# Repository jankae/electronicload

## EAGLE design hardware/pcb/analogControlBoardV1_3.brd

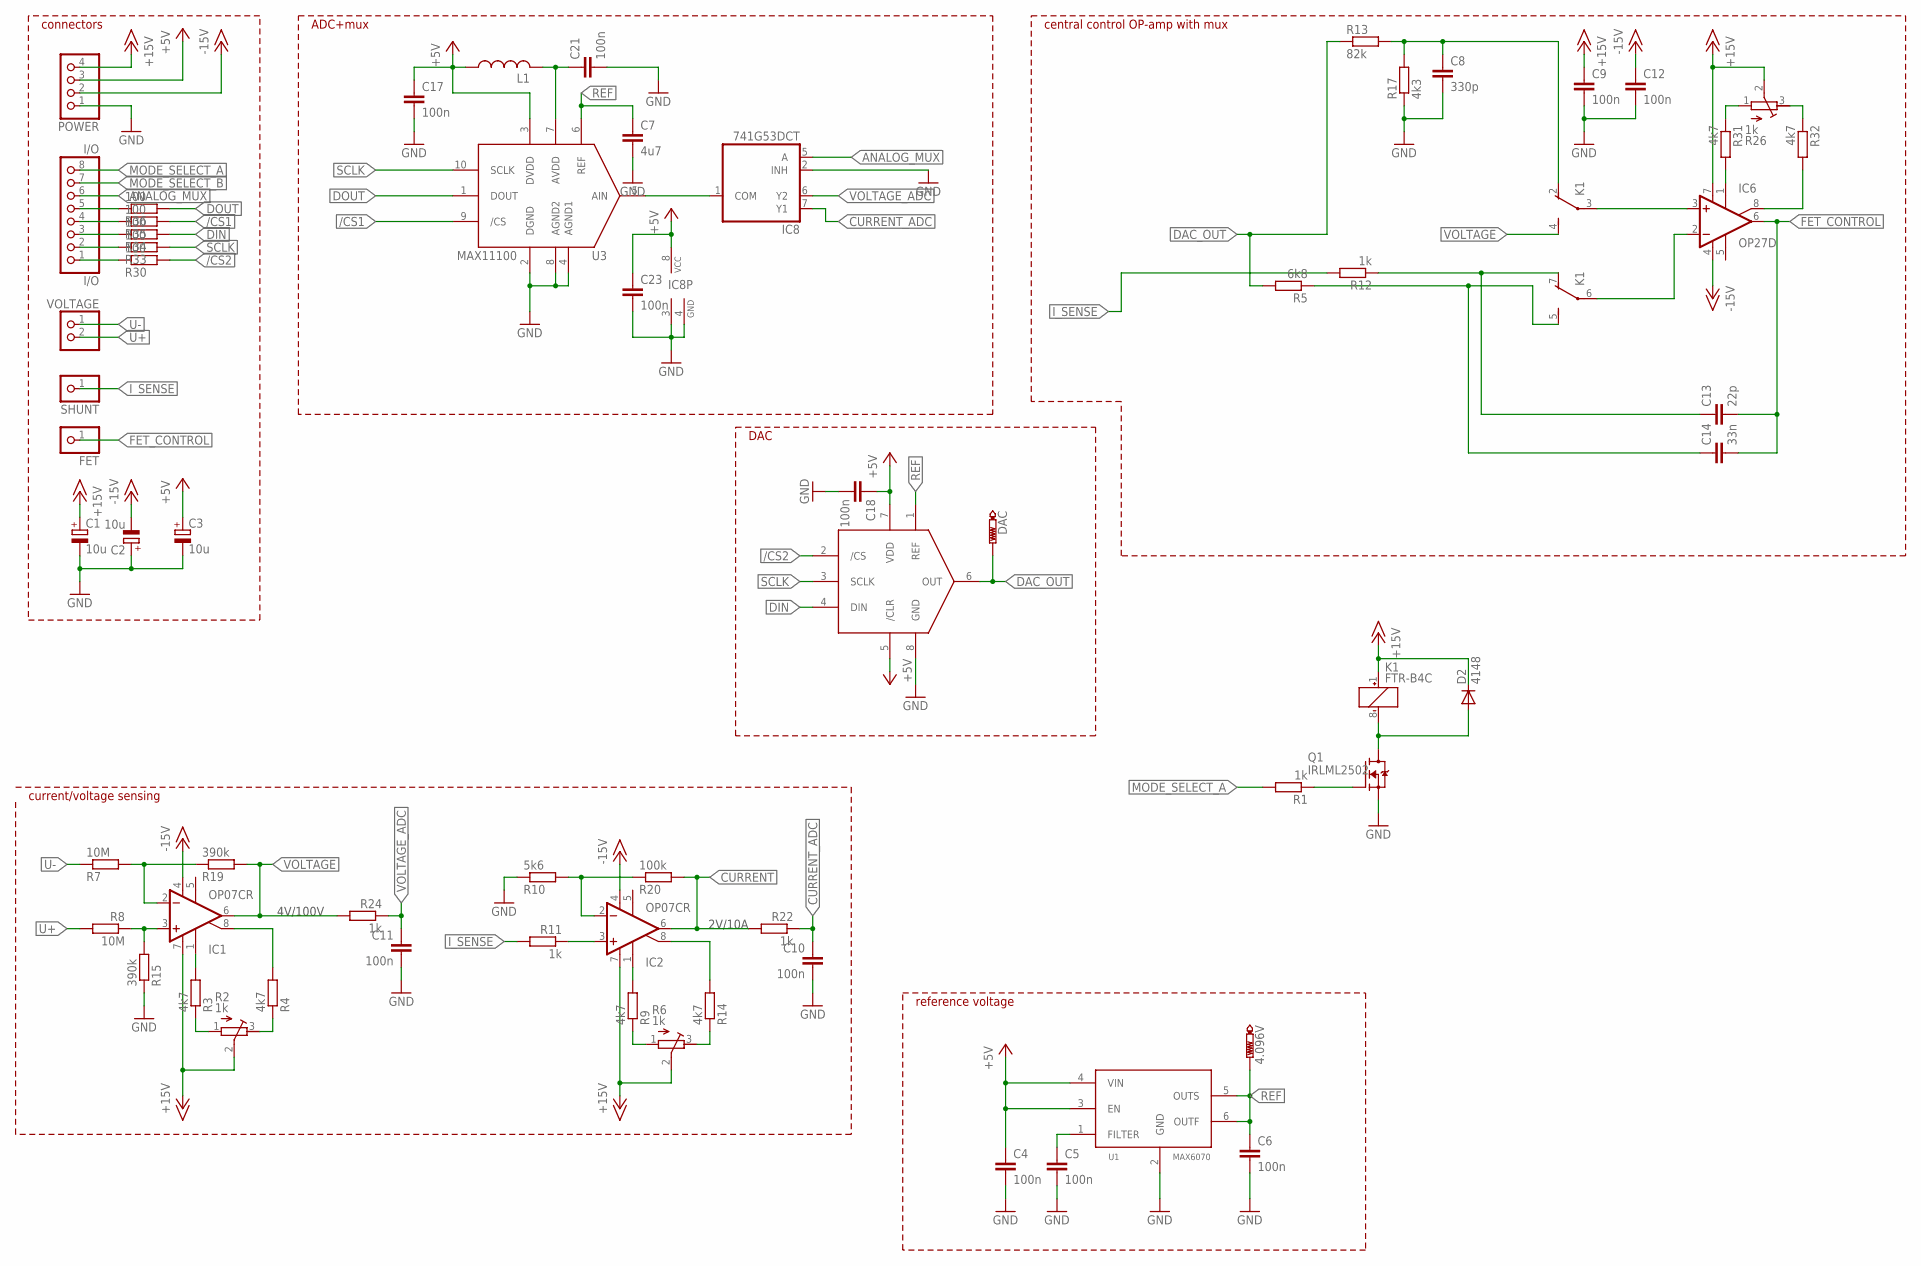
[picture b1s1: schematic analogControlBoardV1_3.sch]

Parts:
4.096V: PTR1TP14R; TP14R
C1, C2, C3: 10u; 153CLV-0505
C4, C5, C6, C9, C10, C11, C12, C17, C18, C21, C23: 100n; C0603K
C7: 4u7; C0805
C8: 330p; C0603K
C13: 22p; C0603K
C14: 33n; C0603K
D2: 4148; SOD123
DAC: PTR1TP14R; TP14R
FET: PINHD-1X1; 1X01
I/O: I/O; 1X08
IC1, IC2: OP07CR; SO08
IC6: OP27D; SO08
IC8: 741G53DCT; DCT_R-PDSO-G8
K1: FTR-B4C
L1: INDUCTOR0603; R0603
POWER: PINHD-1X4; 1X04
Q1: IRLML2502; SOT23-3
R1, R11, R12, R22, R24: 1k; R0603
R2, R6, R26: 1k; RTRIM64W
R3, R4, R9, R14, R31, R32: 4k7; R0603
R5: 6k8; R0603
R7, R8: 10M; R0603
R10: 5k6; R0603
R13: 82k; R0603
R15, R19: 390k; R0603
R17: 4k3; R0603
R20: 100k; R0603
R30, R33, R34, R35, R36: 100; R0603
SHUNT: PINHD-1X1; 1X01
U1: MAX6070; SOT23-6L
U2: MAX5216; UMAX8
U3: MAX11100; UMAX10
VOLTAGE: PINHD-1X2; 1X02

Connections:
+5V: C3.+, C4.1, C17.1, C18.1, C23.1, IC8.8 (VCC), L1.1, POWER.3, U1.3 (EN), U1.4 (VIN), U2.5 (/CLR), U2.7 (VDD), U3.3 (DVDD)
+15V: C1.+, C9.1, D2.C, IC1.7 (V+), IC2.7 (V+), IC6.7 (V+), K1.1 (+), POWER.4, R2.2 (S), R6.2 (S), R26.2 (S)
-15V: C2.-, C12.1, IC1.4 (V-), IC2.4 (V-), IC6.4 (V-), POWER.2
/CS1: R35.2, U3.9 (/CS)
/CS2: R30.2, U2.2 (/CS)
ANALOG_MUX: I/O.6, IC8.5 (A)
CURRENT: IC2.6 (OUT), R20.2, R22.2
CURRENT_ADC: C10.1, IC8.7 (Y1), R22.1
DAC_OUT: DAC.TP, R5.2, R13.1, U2.6 (OUT)
DIN: R34.2, U2.4 (DIN)
DOUT: R36.2, U3.1 (DOUT)
FET_CONTROL: C13.2, C14.2, FET.1, IC6.6 (OUT)
GND: C1.-, C2.+, C3.-, C4.2, C5.2, C6.2, C7.2, C8.2, C9.2, C10.2, C11.2, C12.2, C17.2, C18.2, C21.2, C23.2, IC8.2 (INH), IC8.3 (GND), IC8.4 (GND), POWER.1, Q1.2 (S), R10.1, R15.1, R17.1, U1.2 (GND), U2.8 (GND), U3.2 (DGND), U3.4 (AGND1), U3.8 (AGND2)
I_SENSE: R11.2, R12.2, SHUNT.1
MODE_SELECT_A: I/O.8, R1.2
MODE_SELECT_B: I/O.7
unnamed: C8.1, K1.2 (O), R13.2, R17.2
unnamed: D2.A, K1.8 (-), Q1.3 (D)
unnamed: Q1.1 (G), R1.1
unnamed: C13.1, K1.7 (O), R12.1
unnamed: IC2.3 (+IN), R11.1
unnamed: IC2.2 (-IN), R10.2, R20.1
unnamed: R2.1 (E), R3.1
unnamed: IC1.8 (ON2), R4.2
unnamed: R26.3 (A), R32.1
unnamed: R2.3 (A), R4.1
unnamed: IC6.1 (ON1), R31.2
unnamed: IC1.1 (ON1), R3.2
unnamed: R6.1 (E), R9.1
unnamed: IC2.8 (ON2), R14.2
unnamed: R6.3 (A), R14.1
unnamed: IC2.1 (ON1), R9.2
unnamed: I/O.5, R36.1
unnamed: I/O.4, R35.1
unnamed: I/O.3, R34.1
unnamed: I/O.2, R33.1
unnamed: I/O.1, R30.1
unnamed: IC6.3 (+IN), K1.3
unnamed: C5.1, U1.1 (FILTER)
unnamed: IC6.2 (-IN), K1.6
unnamed: C14.1, K1.5 (S), R5.1
unnamed: R26.1 (E), R31.1
unnamed: IC6.8 (ON2), R32.2
unnamed: C21.1, L1.2, U3.7 (AVDD)
unnamed: IC8.1 (COM), U3.5 (AIN)
unnamed: IC1.3 (+IN), R8.1, R15.2
unnamed: IC1.2 (-IN), R7.2, R19.1
REF: 4.096V.TP, C6.1, C7.1, U1.5 (OUTS), U1.6 (OUTF), U2.1 (REF), U3.6 (REF)
SCLK: R33.2, U2.3 (SCLK), U3.10 (SCLK)
U+: R8.2, VOLTAGE.2
U-: R7.1, VOLTAGE.1
VOLTAGE: IC1.6 (OUT), K1.4 (S), R19.2, R24.2
VOLTAGE_ADC: C11.1, IC8.6 (Y2), R24.1

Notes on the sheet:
2V/10A
4V/100V
connectors
ADC+mux
DAC
current/voltage sensing
reference voltage
central control OP-amp with mux

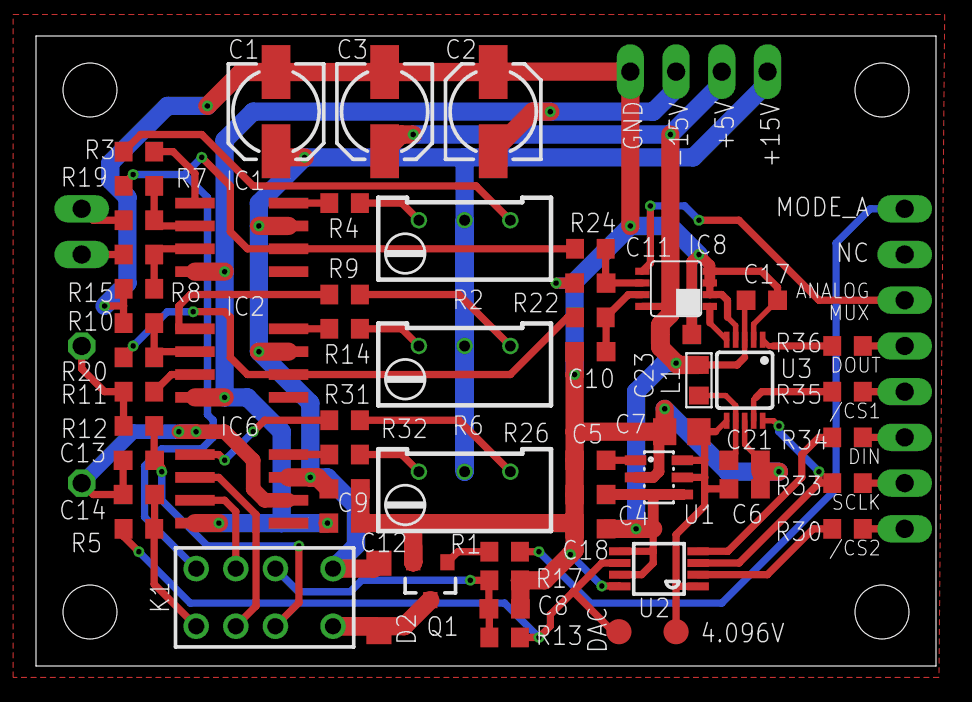
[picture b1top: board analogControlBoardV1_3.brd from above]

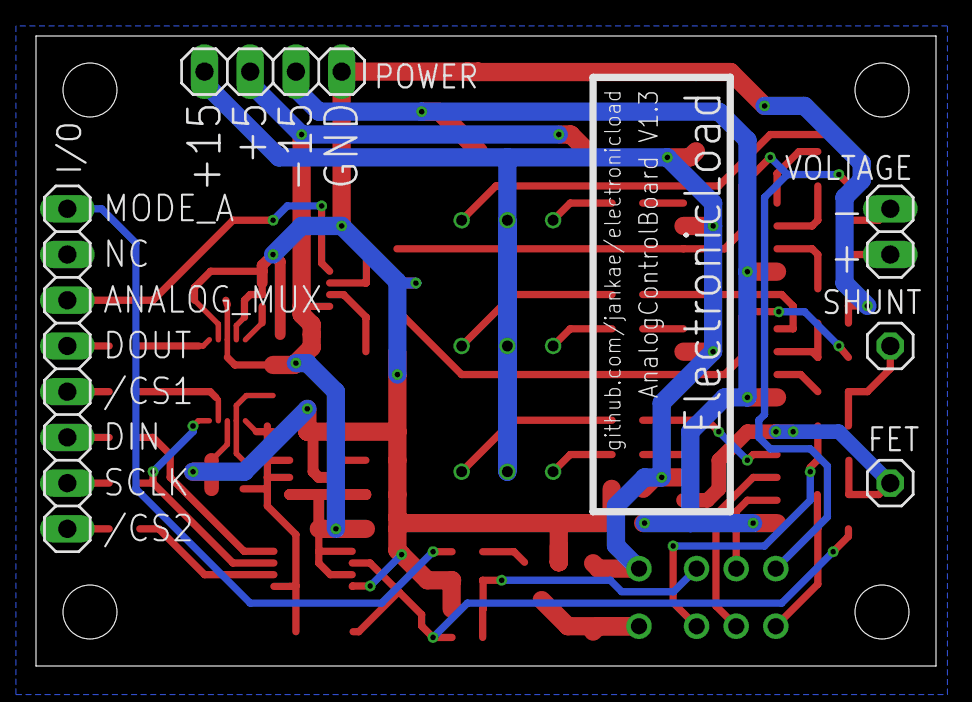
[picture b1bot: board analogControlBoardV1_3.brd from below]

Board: 2 copper layers, 50.0 x 35.0 mm, 64 parts (5 on the bottom side), 52 nets.

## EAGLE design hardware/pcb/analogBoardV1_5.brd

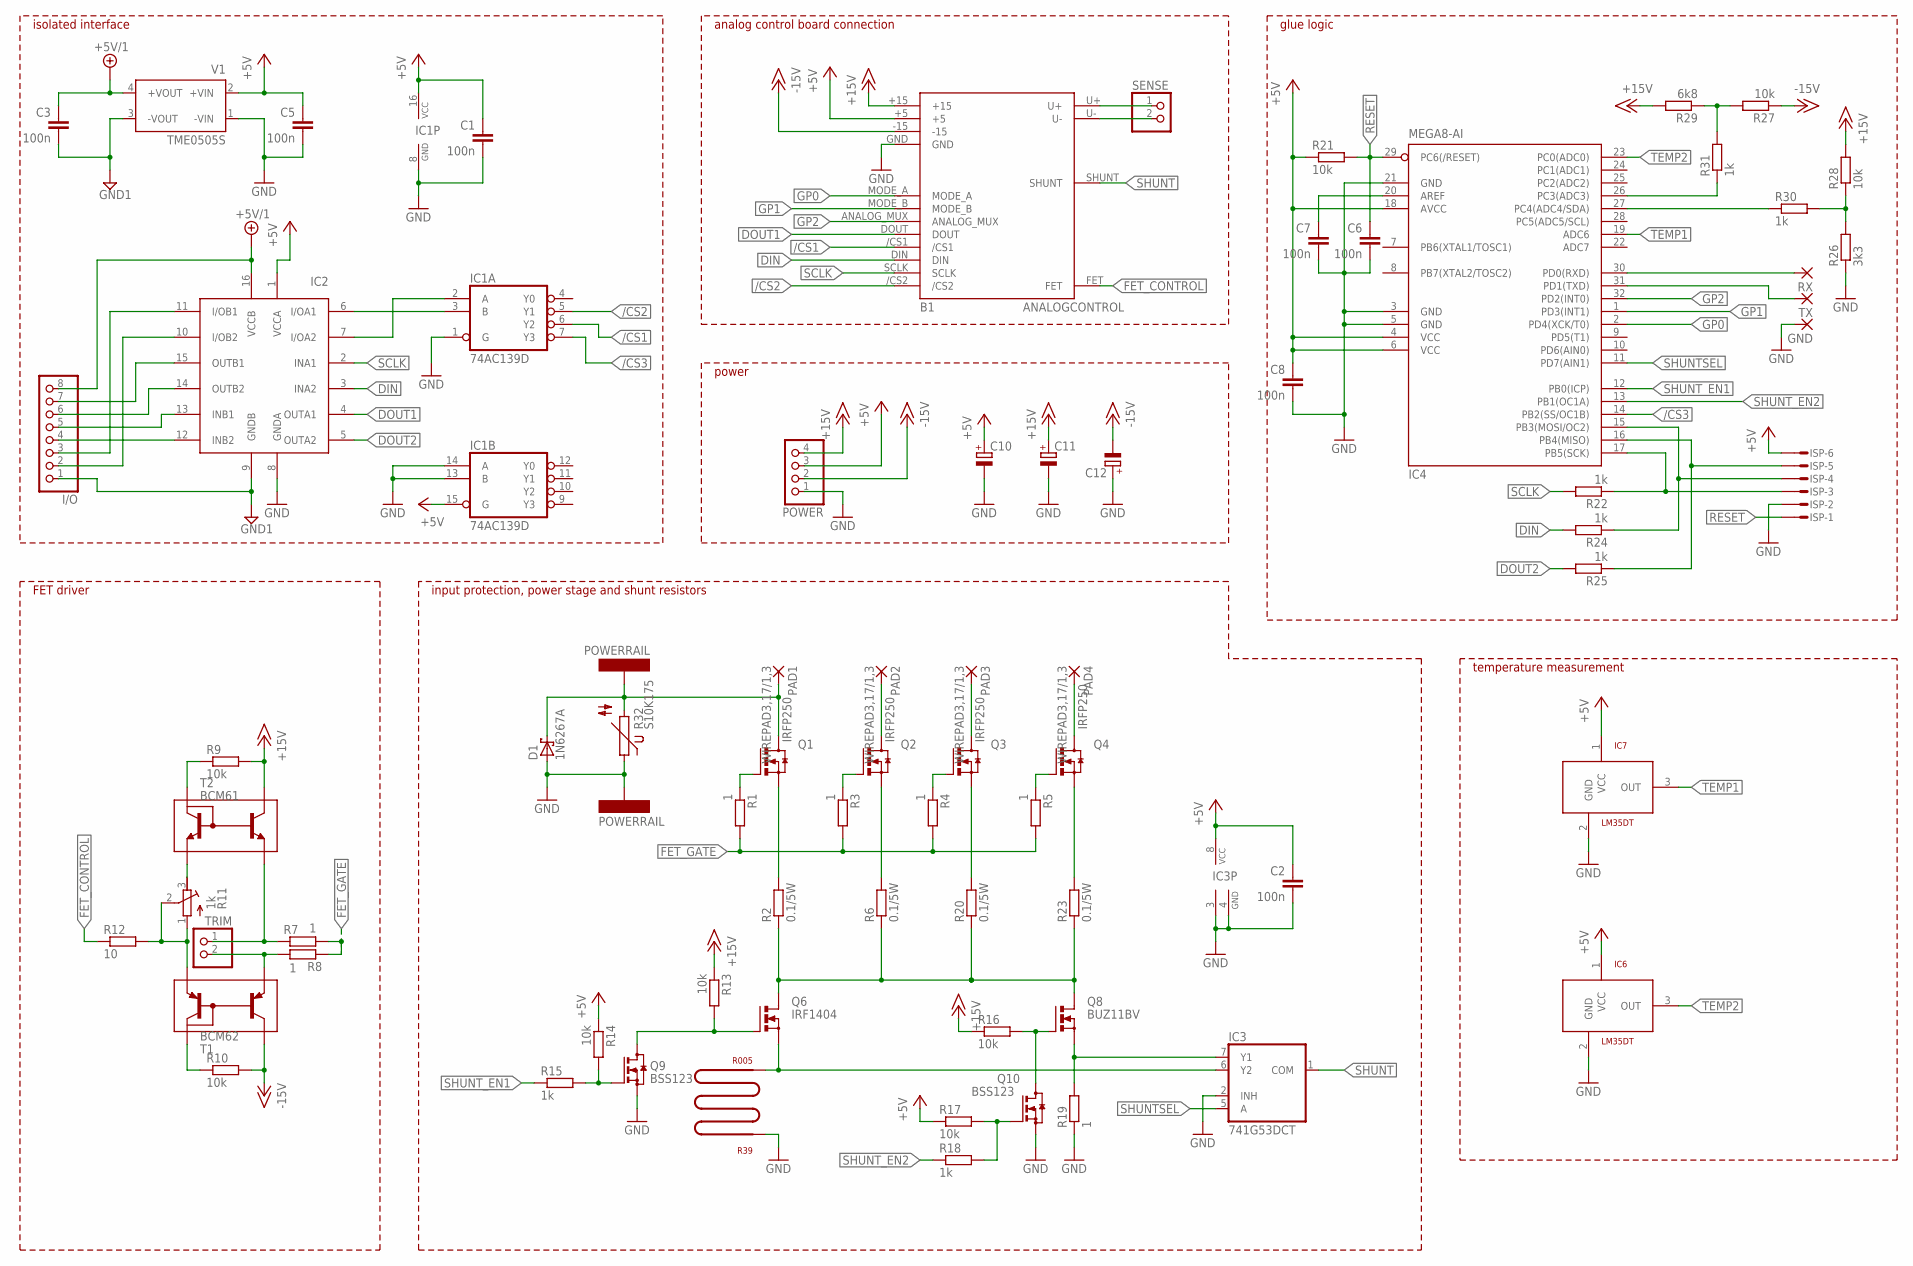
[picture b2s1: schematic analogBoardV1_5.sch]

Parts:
B1: ANALOGCONTROL
C1, C2, C3, C5, C6, C7, C8: 100n; C0603K
C10, C11, C12: CPOL-EUE2.5-6; E2,5-6
D1: 1N6267A; C4111-15
GND: SMD2; SMD1,27-2,54
I/O: PINHD-1X8; 1X08
IC1: 74AC139D; SO16
IC2: MAX14850; SOIC16N
IC3: 741G53DCT; DCT_R-PDSO-G8
IC4: MEGA8-AI; TQFP32-08
IC6, IC7: LM35DT; TO220V
ISP: MICROMATCH-6SMF; MMT-F-SMD-6
PAD1, PAD2, PAD3, PAD4: WIREPAD3,17/1,3; 3,17/1,3
POWER: PINHD-1X4; 1X04
Q1, Q2, Q3, Q4: IRFP250; TO-247AD-V
Q6: IRF1404; TO220BV
Q8: BUZ11BV; TO220BV
Q9, Q10: BSS123; SOT23
R1, R3, R4, R5, R7, R8: 1; R0603
R2, R6, R20, R23: 0.1/5W; 5WAXIAL_H
R9, R10, R13, R14, R16, R17, R21, R27, R28: 10k; R0603
R11: 1k; RTRIM64W
R12: 10; R0603
R15, R18, R22, R24, R25, R30, R31: 1k; R0603
R19: 1; 0414/15
R26: 3k3; R0603
R29: 6k8; R0603
R32: S10K175
R39: R005; PWR4412-2S
RX: SMD2; SMD1,27-2,54
SENSE: PINHD-1X2; 1X02
T1: BCM62; SOT143B
T2: BCM61; SOT143B
TRIM: PINHD-1X2; 1X02
TX: SMD2; SMD1,27-2,54
U$1, U$2: POWERRAIL
V1: TME0505S; TME

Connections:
+5V: B1.+5, C1.1, C2.1, C5.1, C8.1, C10.+, IC1.15 (G), IC1.16 (VCC), IC2.1 (VCCA), IC3.8 (VCC), IC4.4 (VCC), IC4.6 (VCC), IC4.18 (AVCC), IC6.1 (VCC), IC7.1 (VCC), ISP.6, POWER.3, R14.1, R17.1, R21.1, V1.2 (+VIN)
+5V/1: C3.1, I/O.8, IC2.16 (VCCB), V1.4 (+VOUT)
+15V: B1.+15, C11.+, POWER.4, R9.2, R13.1, R16.1, R28.2, R29.2, T2.2
-15V: B1.-15, C12.-, POWER.2, R10.2, R27.1, T1.2
/CS1: B1./CS1, IC1.6 (Y2)
/CS2: B1./CS2, IC1.5 (Y1)
/CS3: IC1.7 (Y3), IC4.14 (PB2(SS/OC1B))
DIN: B1.DIN, IC2.3 (INA2), R24.2
DOUT1: B1.DOUT, IC2.4 (OUTA1)
DOUT2: IC2.5 (OUTA2), R25.2
FET_CONTROL: B1.FET, R12.1
FET_GATE: R1.2, R3.2, R4.2, R5.2, R7.2, R8.1
GND: B1.GND, C1.2, C2.2, C5.2, C6.2, C7.2, C8.2, C10.-, C11.-, C12.+, D1.A, GND.1, IC1.1 (G), IC1.8 (GND), IC1.13 (B), IC1.14 (A), IC2.8 (GNDA), IC3.2 (INH), IC3.3 (GND), IC3.4 (GND), IC4.3 (GND), IC4.5 (GND), IC4.21 (GND), IC6.2 (GND), IC7.2 (GND), ISP.2, POWER.1, Q9.2 (S), Q10.2 (S), R19.1, R26.1, R32.1, R39.P$1, U$2.1, V1.1 (-VIN)
GND1: C3.2, I/O.1, IC2.9 (GNDB), V1.3 (-VOUT)
GP0: B1.MODE_A, IC4.2 (PD4(XCK/T0))
GP1: B1.MODE_B, IC4.1 (PD3(INT1))
GP2: B1.ANALOG_MUX, IC4.32 (PD2(INT0))
N: Q6.D, Q8.D, R2.1, R6.1, R20.1, R23.1
unnamed: R9.1, T2.1
unnamed: Q1.G, R1.1
unnamed: Q1.S, R2.2
unnamed: Q4.G, R5.1
unnamed: Q3.G, R4.1
unnamed: Q2.G, R3.1
unnamed: I/O.4, IC2.12 (INB2)
unnamed: Q2.S, R6.2
unnamed: R7.1, T2.3, TRIM.1
unnamed: R8.2, T1.3, TRIM.2
unnamed: R10.1, T1.1
unnamed: I/O.5, IC2.13 (INB1)
unnamed: R11.3 (A), T2.4
unnamed: I/O.6, IC2.14 (OUTB2)
unnamed: I/O.7, IC2.15 (OUTB1)
unnamed: B1.U+, SENSE.1
unnamed: Q6.G, Q9.3 (D), R13.2
unnamed: Q3.S, R20.2
unnamed: R11.1 (E), R11.2 (S), R12.2, T1.4
unnamed: IC1.3 (B), IC2.6 (I/OA1)
unnamed: Q9.1 (G), R14.2, R15.2
unnamed: Q8.G, Q10.3 (D), R16.2
unnamed: Q10.1 (G), R17.2, R18.2
unnamed: PAD2.1, Q2.D
unnamed: IC1.2 (A), IC2.7 (I/OA2)
unnamed: Q4.S, R23.2
unnamed: I/O.3, IC2.11 (I/OB1)
unnamed: I/O.2, IC2.10 (I/OB2)
unnamed: PAD3.1, Q3.D
unnamed: C7.1, IC4.20 (AREF)
unnamed: IC4.30 (PD0(RXD)), RX.1
unnamed: IC4.31 (PD1(TXD)), TX.1
unnamed: R26.2, R28.1, R30.2
unnamed: R27.2, R29.1, R31.2
unnamed: IC4.27 (PC4(ADC4/SDA)), R30.1
unnamed: IC4.26 (PC3(ADC3)), R31.1
unnamed: B1.U-, SENSE.2
unnamed: IC4.15 (PB3(MOSI/OC2)), ISP.4, R24.1
unnamed: IC4.17 (PB5(SCK)), ISP.3, R22.1
unnamed: IC4.16 (PB4(MISO)), ISP.5, R25.1
POS_INPUT1: PAD4.1, Q4.D
RESET: C6.1, IC4.29 (PC6(/RESET)), ISP.1, R21.2
SCLK: B1.SCLK, IC2.2 (INA1), R22.2
SHUNT: B1.SHUNT, IC3.1 (COM)
SHUNT1: IC3.6 (Y2), Q6.S, R39.P$2
SHUNT2: IC3.7 (Y1), Q8.S, R19.2
SHUNTSEL: IC3.5 (A), IC4.11 (PD7(AIN1))
SHUNT_EN1: IC4.12 (PB0(ICP)), R15.1
SHUNT_EN2: IC4.13 (PB1(OC1A)), R18.1
TEMP1: IC4.19 (ADC6), IC7.3 (OUT)
TEMP2: IC4.23 (PC0(ADC0)), IC6.3 (OUT)
VIN: D1.C, PAD1.1, Q1.D, R32.2, U$1.1

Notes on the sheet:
FET driver
input protection, power stage and shunt resistors
temperature measurement
power
analog control board connection
glue logic
isolated interface

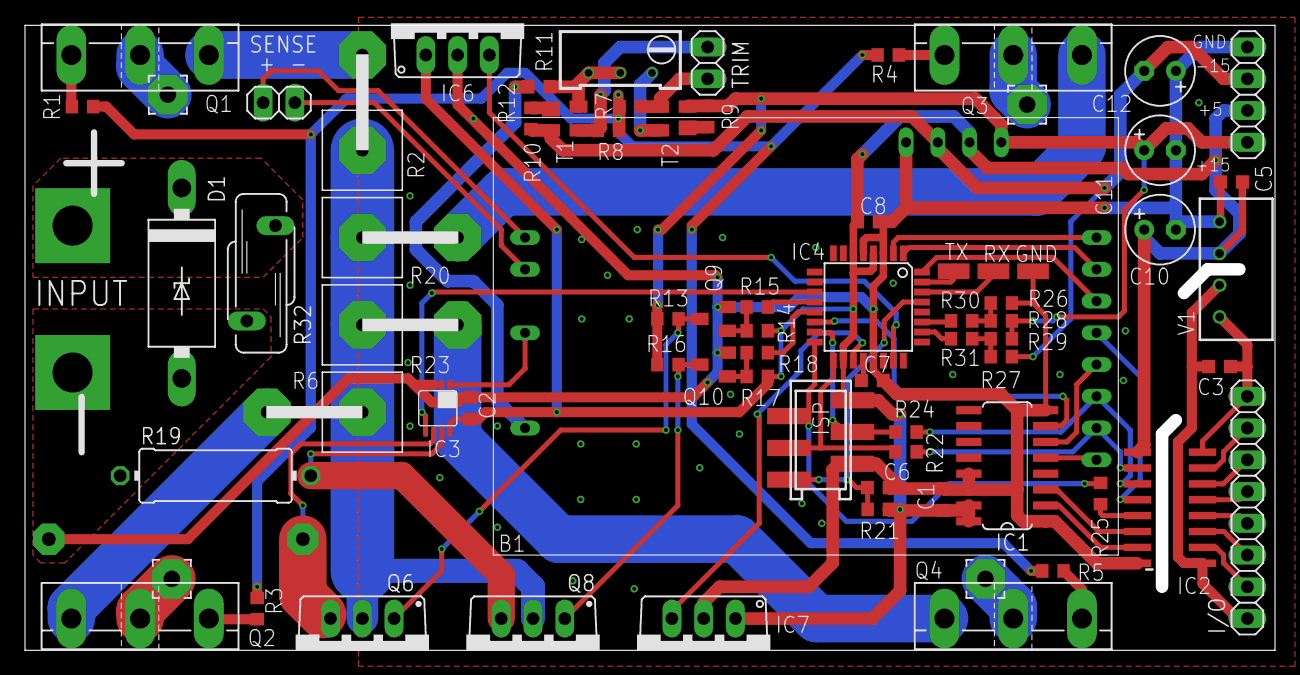
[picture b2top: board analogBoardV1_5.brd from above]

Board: 2 copper layers, 99.0 x 49.0 mm, 76 parts (0 on the bottom side), 70 nets.

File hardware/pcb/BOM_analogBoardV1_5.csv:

"Qty";"Value";"Device";"Package";"Parts";"Description";"MF";"MPN";"OC_FARNELL";"OC_NEWARK";
"3";"";"CPOL-EUE2.5-6";"E2,5-6";"C10, C11, C12";"POLARIZED CAPACITOR, European symbol";"";"";"";"";
"1";"";"MAX14850";"SOIC16N";"IC2";"";"";"";"";"";
"1";"";"MICROMATCH-6SMF";"MMT-F-SMD-6";"ISP";"MicroMaTch 6  7-215464-6 / 0-215464-6";"";"";"";"";
"2";"";"PINHD-1X2";"1X02";"SENSE, TRIM";"PIN HEADER";"";"";"";"";
"1";"";"PINHD-1X4";"1X04";"POWER";"PIN HEADER";"";"";"";"";
"1";"";"PINHD-1X8";"1X08";"I/O";"PIN HEADER";"";"";"";"";
"3";"";"SMD2";"SMD1,27-2,54";"GND, RX, TX";"SMD PAD";"";"";"";"";
"4";"0.1/5W";"5WAXIALH";"5WAXIAL_H";"R2, R6, R20, R23";"";"";"";"";"";
"1";"1";"R-EU_0414/15";"0414/15";"R19";"RESISTOR, European symbol";"";"";"";"";
"6";"1";"R-EU_R0603";"R0603";"R1, R3, R4, R5, R7, R8";"RESISTOR, European symbol";"";"";"";"";
"1";"10";"R-EU_R0603";"R0603";"R12";"RESISTOR, European symbol";"";"";"";"";
"7";"100n";"C-EUC0603K";"C0603K";"C1, C2, C3, C5, C6, C7, C8";"CAPACITOR, European symbol";"";"";"";"";
"9";"10k";"R-EU_R0603";"R0603";"R9, R10, R13, R14, R16, R17, R21, R27, R28";"RESISTOR, European symbol";"";"";"";"";
"1";"1N6267A";"1N6267A";"C4111-15";"D1";"DIODE";"";"";"";"";
"7";"1k";"R-EU_R0603";"R0603";"R15, R18, R22, R24, R25, R30, R31";"RESISTOR, European symbol";"";"";"";"";
"1";"1k";"R-TRIMM64W";"RTRIM64W";"R11";"Trimm resistor";"";"";"";"";
"1";"3k3";"R-EU_R0603";"R0603";"R26";"RESISTOR, European symbol";"";"";"";"";
"1";"6k8";"R-EU_R0603";"R0603";"R29";"RESISTOR, European symbol";"";"";"";"";
"1";"741G53DCT";"741G53DCT";"DCT_R-PDSO-G8";"IC3";"SINGLE-POLE DOUBLE-THROW (SPDT) ANALOG SWITCH 2:1 ANALOG MULTIPLEXER/DEMULTIPLEXER";"";"";"";"";
"1";"74AC139D";"74AC139D";"SO16";"IC1";"Dual 2-line to 4-line DECODER/DEMULTIPLEXER";"";"";"";"";
"1";"ANALOGCONTROL";"ANALOGCONTROL";"ANALOGCONTROL";"B1";"";"";"";"";"";
"1";"BCM61";"BCM61";"SOT143B";"T2";"";"";"";"";"";
"1";"BCM62";"BCM62";"SOT143B";"T1";"";"";"";"";"";
"2";"BSS123";"BSS123";"SOT23";"Q9, Q10";"N-CHANNEL MOS FET";"";"";"";"";
"1";"BUZ11BV";"BUZ11BV";"TO220BV";"Q8";"N-CHANNEL MOS FET";"";"";"";"";
"1";"IRF1404";"BUZ11BV";"TO220BV";"Q6";"N-CHANNEL MOS FET";"";"";"";"";
"4";"IRFP250";"IRFP250";"TO-247AD-V";"Q1, Q2, Q3, Q4";"33A/27A, 200V/150V, 0.085/0.012 Ohm, N-Channel Power MOSFET";"";"";"";"";
"2";"LM35DT";"LM35DT";"TO220V";"IC6, IC7";"";"";"";"";"";
"1";"MEGA8-AI";"MEGA8-AI";"TQFP32-08";"IC4";"MICROCONTROLLER";"";"ATMEGA8-16AU";"9171371";"73M8863";
"2";"POWERRAIL";"POWERRAIL";"POWERRAIL";"U$1, U$2";"";"";"";"";"";
"1";"R005";"SHUNTPWR";"PWR4412-2S";"R39";"";"";"";"";"";
"1";"S10K175";"S10K175";"S10K175";"R32";"VARISTOR";"";"";"";"";
"1";"TME0505S";"TME0505S";"TME";"V1";"DC/DC Converter TME Series 1 Watt";"";"TME 0505S";"1007538";"51R5321";
"4";"WIREPAD3,17/1,3";"WIREPAD3,17/1,3";"3,17/1,3";"PAD1, PAD2, PAD3, PAD4";"Wire PAD connect wire on PCB";"";"";"";"";

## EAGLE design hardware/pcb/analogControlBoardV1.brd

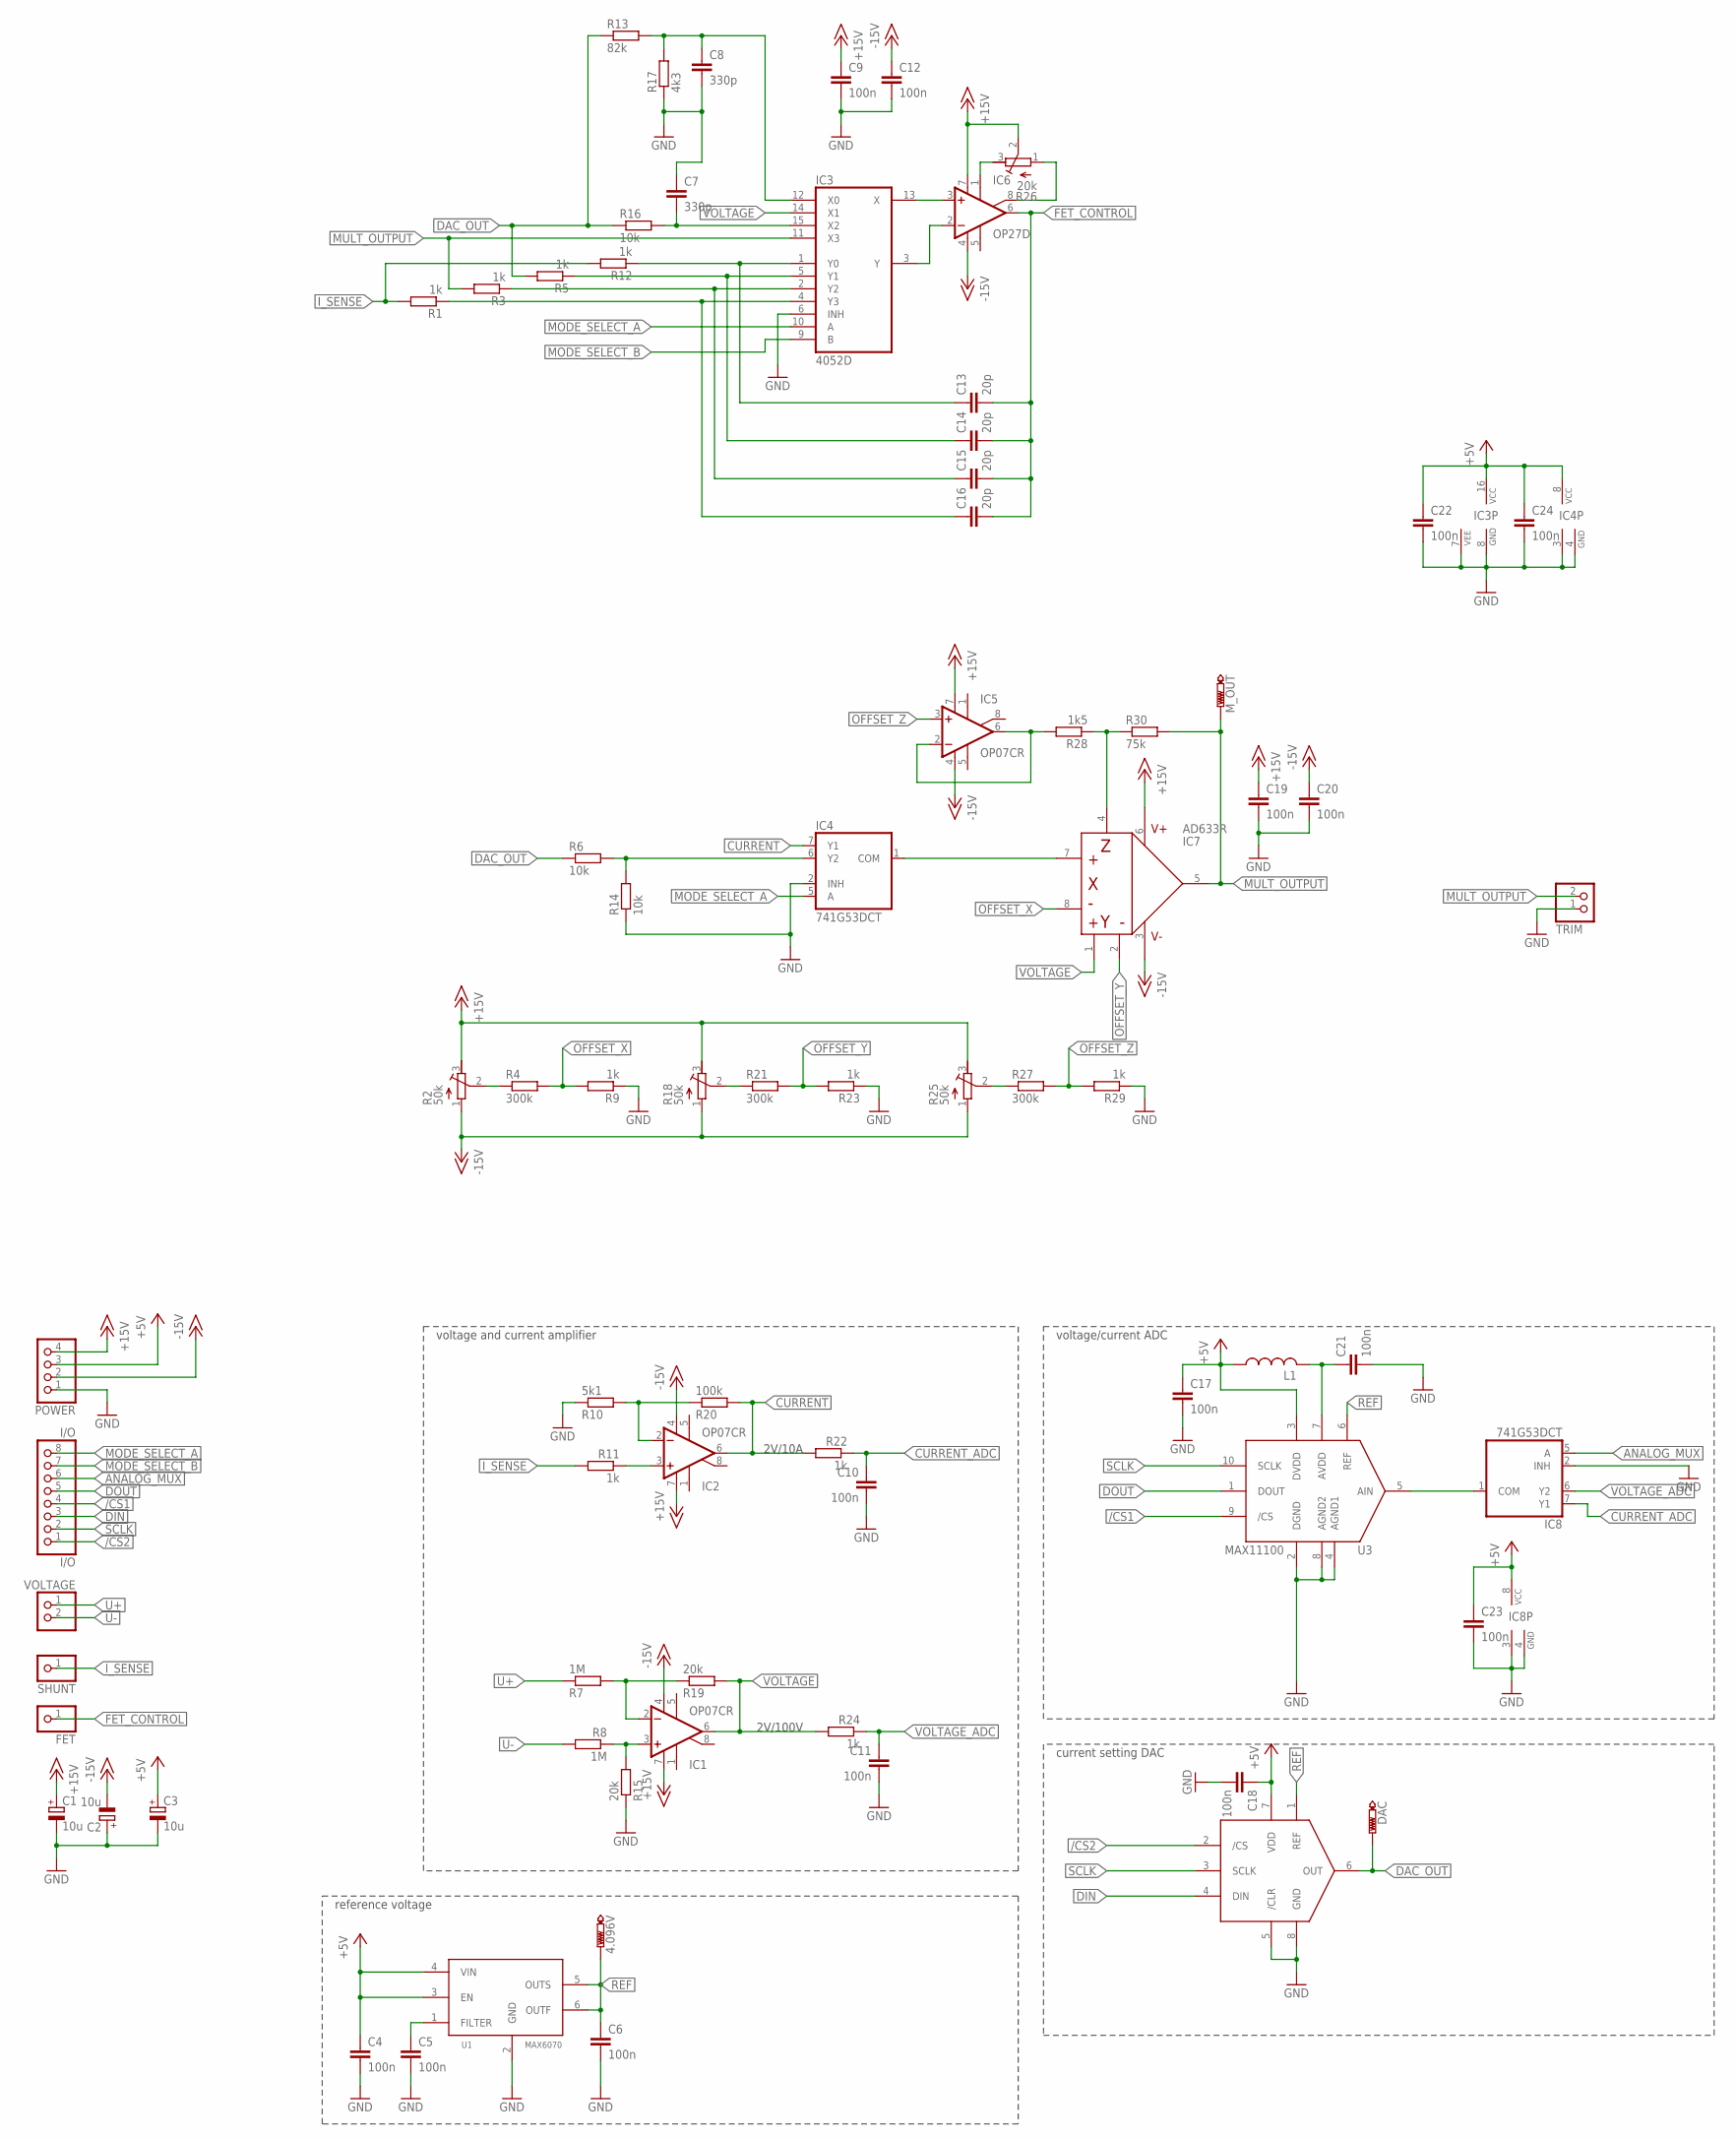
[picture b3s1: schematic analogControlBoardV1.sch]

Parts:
4.096V: PTR1TP06R; TP06R
C1, C2, C3: 10u; 153CLV-0505
C4, C5, C6, C9, C10, C11, C12, C17, C18, C19, C20, C21, C22, C23, C24: 100n; C0603K
C7, C8: 330p; C0603K
C13, C14, C15, C16: 20p; C0603K
DAC: PTR1TP06R; TP06R
FET: PINHD-1X1; 1X01
I/O: I/O; 1X08
IC1, IC2, IC5: OP07CR; SO08
IC3: 4052D; SO16
IC4, IC8: 741G53DCT; DCT_R-PDSO-G8
IC6: OP27D; SO08
IC7: AD633R; SO08
L1: INDUCTOR0603; R0603
M_OUT: PTR1TP06R; TP06R
POWER: PINHD-1X4; 1X04
R1, R3, R5, R9, R11, R12, R22, R23, R24, R29: 1k; R0603
R2, R18, R25: 50k; RTRIM64W
R4, R21, R27: 300k; R0603
R6, R14, R16: 10k; R0603
R7, R8: 1M; R0603
R10: 5k1; R0603
R13: 82k; R0603
R15, R19: 20k; R0603
R17: 4k3; R0603
R20: 100k; R0603
R26: 20k; RTRIM64W
R28: 1k5; R0603
R30: 75k; R0603
SHUNT: PINHD-1X1; 1X01
TRIM: PINHD-1X2; 1X02
U1: MAX6070; SOT23-6L
U2: MAX5216; UMAX8
U3: MAX11100; UMAX10
VOLTAGE: PINHD-1X2; 1X02

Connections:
+5V: C3.+, C4.1, C17.1, C18.1, C22.1, C23.1, C24.1, IC3.16 (VCC), IC4.8 (VCC), IC8.8 (VCC), L1.1, POWER.3, U1.3 (EN), U1.4 (VIN), U2.7 (VDD), U3.3 (DVDD)
+15V: C1.+, C9.1, C19.1, IC1.7 (V+), IC2.7 (V+), IC5.7 (V+), IC6.7 (V+), IC7.6 (V+), POWER.4, R2.3 (A), R18.3 (A), R25.3 (A), R26.2 (S)
-15V: C2.-, C12.1, C20.1, IC1.4 (V-), IC2.4 (V-), IC5.4 (V-), IC6.4 (V-), IC7.3 (V-), POWER.2, R2.1 (E), R18.1 (E), R25.1 (E)
/CS1: I/O.4, U3.9 (/CS)
/CS2: I/O.1, U2.2 (/CS)
ANALOG_MUX: I/O.6, IC8.5 (A)
CURRENT: IC2.6 (OUT), IC4.7 (Y1), R20.2, R22.2
CURRENT_ADC: C10.1, IC8.7 (Y1), R22.1
DAC_OUT: DAC.TP, R5.2, R6.1, R13.1, R16.1, U2.6 (OUT)
DIN: I/O.3, U2.4 (DIN)
DOUT: I/O.5, U3.1 (DOUT)
FET_CONTROL: C13.2, C14.2, C15.2, C16.2, FET.1, IC6.6 (OUT)
GND: C1.-, C2.+, C3.-, C4.2, C5.2, C6.2, C7.1, C8.2, C9.2, C10.2, C11.2, C12.2, C17.2, C18.2, C19.2, C20.2, C21.2, C22.2, C23.2, C24.2, IC3.6 (INH), IC3.7 (VEE), IC3.8 (GND), IC4.2 (INH), IC4.3 (GND), IC4.4 (GND), IC8.2 (INH), IC8.3 (GND), IC8.4 (GND), POWER.1, R9.1, R10.1, R14.1, R15.1, R17.1, R23.1, R29.1, TRIM.1, U1.2 (GND), U2.5 (/CLR), U2.8 (GND), U3.2 (DGND), U3.4 (AGND1), U3.8 (AGND2)
I_SENSE: R1.2, R11.2, R12.2, SHUNT.1
MODE_SELECT_A: I/O.8, IC3.10 (A), IC4.5 (A)
MODE_SELECT_B: I/O.7, IC3.9 (B)
MULT_OUTPUT: IC3.11 (X3), IC7.5 (OUT), M_OUT.TP, R3.2, R30.2, TRIM.2
unnamed: C8.1, IC3.12 (X0), R13.2, R17.2
unnamed: IC7.4 (Z), R28.1, R30.1
unnamed: IC4.6 (Y2), R6.2, R14.2
unnamed: C13.1, IC3.1 (Y0), R12.1
unnamed: IC2.3 (+IN), R11.1
unnamed: IC2.2 (-IN), R10.2, R20.1
unnamed: IC5.2 (-IN), IC5.6 (OUT), R28.2
unnamed: R25.2 (S), R27.1
unnamed: C7.2, IC3.15 (X2), R16.2
unnamed: IC3.13 (X), IC6.3 (+IN)
unnamed: C5.1, U1.1 (FILTER)
unnamed: IC3.3 (Y), IC6.2 (-IN)
unnamed: IC4.1 (COM), IC7.7 (X+)
unnamed: R18.2 (S), R21.1
unnamed: C16.1, IC3.4 (Y3), R1.1
unnamed: R2.2 (S), R4.1
unnamed: C15.1, IC3.2 (Y2), R3.1
unnamed: C14.1, IC3.5 (Y1), R5.1
unnamed: IC6.1 (ON1), R26.3 (A)
unnamed: IC6.8 (ON2), R26.1 (E)
unnamed: C21.1, L1.2, U3.7 (AVDD)
unnamed: IC8.1 (COM), U3.5 (AIN)
unnamed: IC1.3 (+IN), R8.1, R15.2
unnamed: IC1.2 (-IN), R7.2, R19.1
OFFSET_X: IC7.8 (X-), R4.2, R9.2
OFFSET_Y: IC7.2 (Y-), R21.2, R23.2
OFFSET_Z: IC5.3 (+IN), R27.2, R29.2
REF: 4.096V.TP, C6.1, U1.5 (OUTS), U1.6 (OUTF), U2.1 (REF), U3.6 (REF)
SCLK: I/O.2, U2.3 (SCLK), U3.10 (SCLK)
U+: R7.1, VOLTAGE.1
U-: R8.2, VOLTAGE.2
VOLTAGE: IC1.6 (OUT), IC3.14 (X1), IC7.1 (Y+), R19.2, R24.2
VOLTAGE_ADC: C11.1, IC8.6 (Y2), R24.1

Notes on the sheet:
2V/10A
2V/100V
reference voltage
voltage and current amplifier
voltage/current ADC
current setting DAC

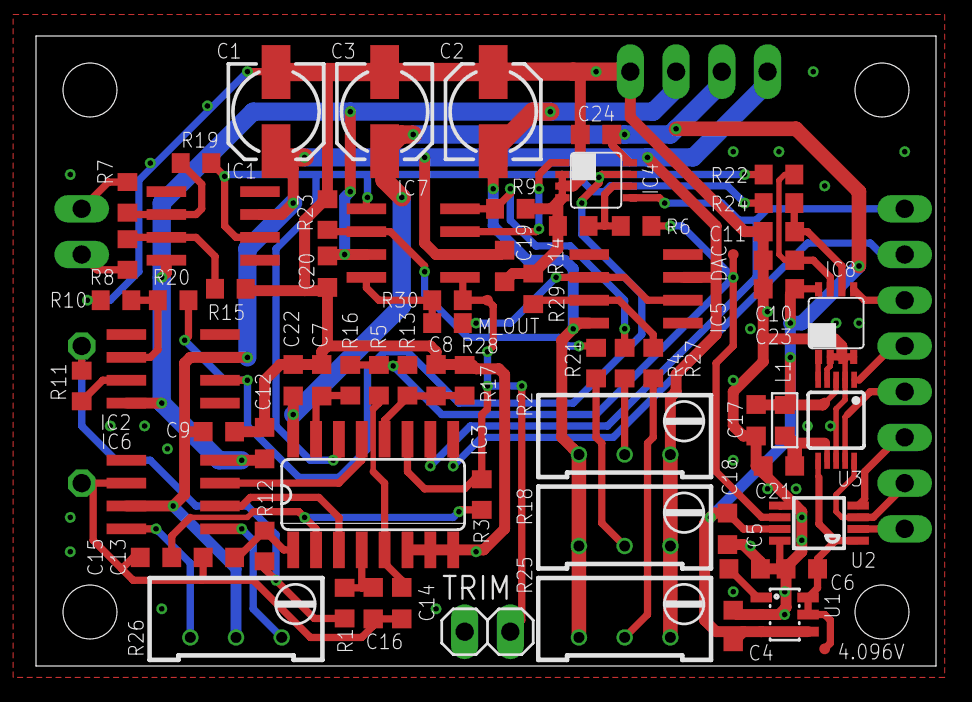
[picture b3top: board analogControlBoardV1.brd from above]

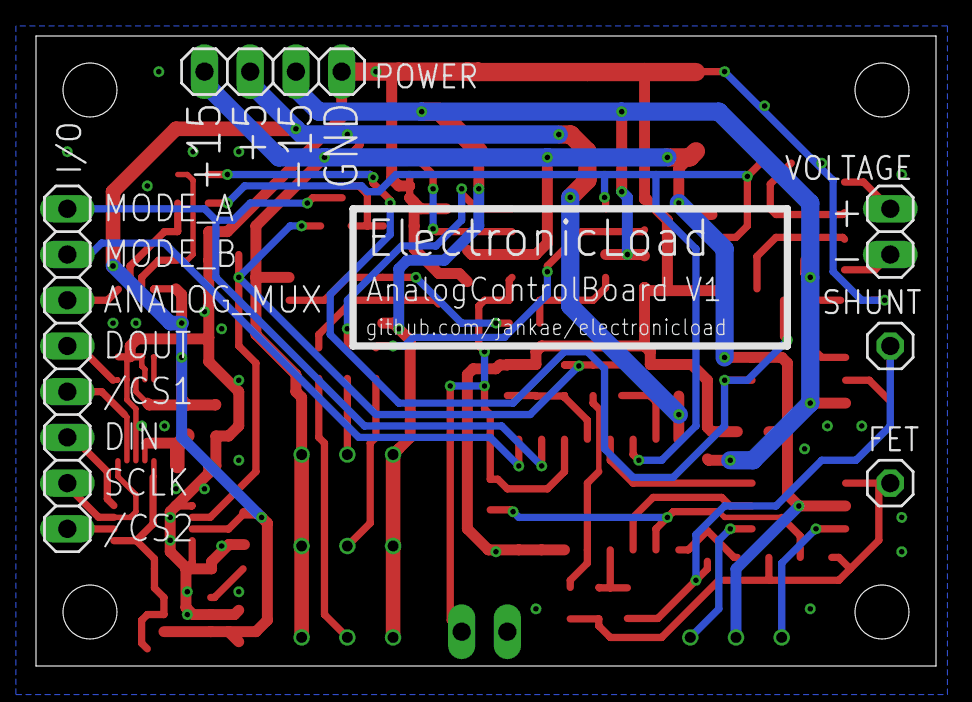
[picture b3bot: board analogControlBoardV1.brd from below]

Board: 2 copper layers, 50.0 x 35.0 mm, 75 parts (5 on the bottom side), 50 nets.

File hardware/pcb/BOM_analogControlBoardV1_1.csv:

"Qty";"Value";"Device";"Package";"Parts";"Description";"TP_SIGNAL_NAME";
"1";"";"INDUCTOR0603";"R0603";"L1";"Inductor";"";
"2";"";"PINHD-1X1";"1X01";"FET, SHUNT";"PIN HEADER";"";
"2";"";"PINHD-1X2";"1X02";"TRIM, VOLTAGE";"PIN HEADER";"";
"1";"";"PINHD-1X4";"1X04";"POWER";"PIN HEADER";"";
"1";"100k";"R-EU_R0603";"R0603";"R20";"RESISTOR, European symbol";"";
"15";"100n";"C-EUC0603K";"C0603K";"C4, C5, C6, C9, C10, C11, C12, C17, C18, C19, C20, C21, C22, C23, C24";"CAPACITOR, European symbol";"";
"3";"10k";"R-EU_R0603";"R0603";"R6, R14, R16";"RESISTOR, European symbol";"";
"3";"10u";"CPOL-EU153CLV-0505";"153CLV-0505";"C1, C2, C3";"POLARIZED CAPACITOR, European symbol";"";
"2";"1M";"R-EU_R0603";"R0603";"R7, R8";"RESISTOR, European symbol";"";
"11";"1k";"R-EU_R0603";"R0603";"R1, R3, R5, R9, R11, R12, R22, R23, R24, R28, R29";"RESISTOR, European symbol";"";
"1";"20k";"R-TRIMM64W";"RTRIM64W";"R26";"Trimm resistor";"";
"4";"20p";"C-EUC0603K";"C0603K";"C13, C14, C15, C16";"CAPACITOR, European symbol";"";
"1";"24k";"R-EU_R0603";"R0603";"R30";"RESISTOR, European symbol";"";
"3";"300k";"R-EU_R0603";"R0603";"R4, R21, R27";"RESISTOR, European symbol";"";
"2";"330p";"C-EUC0603K";"C0603K";"C7, C8";"CAPACITOR, European symbol";"";
"2";"39k";"R-EU_R0603";"R0603";"R15, R19";"RESISTOR, European symbol";"";
"1";"4052D";"4052D";"SO16";"IC3";"Dual 4-channel ANALOG MULTIPLEXER";"";
"1";"4k3";"R-EU_R0603";"R0603";"R17";"RESISTOR, European symbol";"";
"3";"50k";"R-TRIMM64W";"RTRIM64W";"R2, R18, R25";"Trimm resistor";"";
"1";"5k1";"R-EU_R0603";"R0603";"R10";"RESISTOR, European symbol";"";
"2";"741G53DCT";"741G53DCT";"DCT_R-PDSO-G8";"IC4, IC8";"SINGLE-POLE DOUBLE-THROW (SPDT) ANALOG SWITCH 2:1 ANALOG MULTIPLEXER/DEMULTIPLEXER";"";
"1";"82k";"R-EU_R0603";"R0603";"R13";"RESISTOR, European symbol";"";
"1";"AD633R";"AD633R";"SO08";"IC7";"AD633 Multiplier (X*Y)/(10*Z)";"";
"1";"I/O";"PINHD-1X8";"1X08";"I/O";"PIN HEADER";"";
"1";"MAX11100";"MAX11100";"UMAX10";"U3";"";"";
"1";"MAX5216";"MAX5216";"UMAX8";"U2";"";"";
"1";"MAX6070";"MAX6070";"SOT23-6L";"U1";"";"";
"3";"OP07CR";"OP07CR";"SO08";"IC1, IC2, IC5";"OP AMP";"";
"1";"OP27D";"OP27D";"SO08";"IC6";"OP AMP";"";
"3";"PTR1TP06R";"PTR1TP06R";"TP06R";"4.096V, DAC, M_OUT";"TEST PIN";"";

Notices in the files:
parts and their libraries:
xmaker: Licensing: CC v3.0 Attribution-Share Alike
http://creativecommons.org/licenses/by-sa/3.0
